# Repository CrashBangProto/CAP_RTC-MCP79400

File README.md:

#Toadstool-RTC79400

**Toadstool Cap - MCP79400 Real time clock**

The Toadstool family is made up of breadboard-friendly prototyping boards that house a microcontroller, and modules called *Caps* that connect using a standard header.  The prototyping board is analagous to an Arduino/Launchpad and the Cap analagous to a shield/boosterpack.

This repository contains the schematics for the **Toadstool-RTC79400 Cap**, a Real Time Clock module that connects to  Toadstool prototyping boards using the common header.  The Microchip MCP79400 chip does all the work.

The boards were layed out using [KiCad](http://www.kicad-pcb.org) - KiCad is open source and awesome.

There are a number of other CrashBangProto respositories containing the schematics for other Toadstool boards and Caps, as well as sample code to get you up and running.

Visit the [Toadstool Webpages](http://www.crash-bang.com/projects/toadstool/) for more information on the project.

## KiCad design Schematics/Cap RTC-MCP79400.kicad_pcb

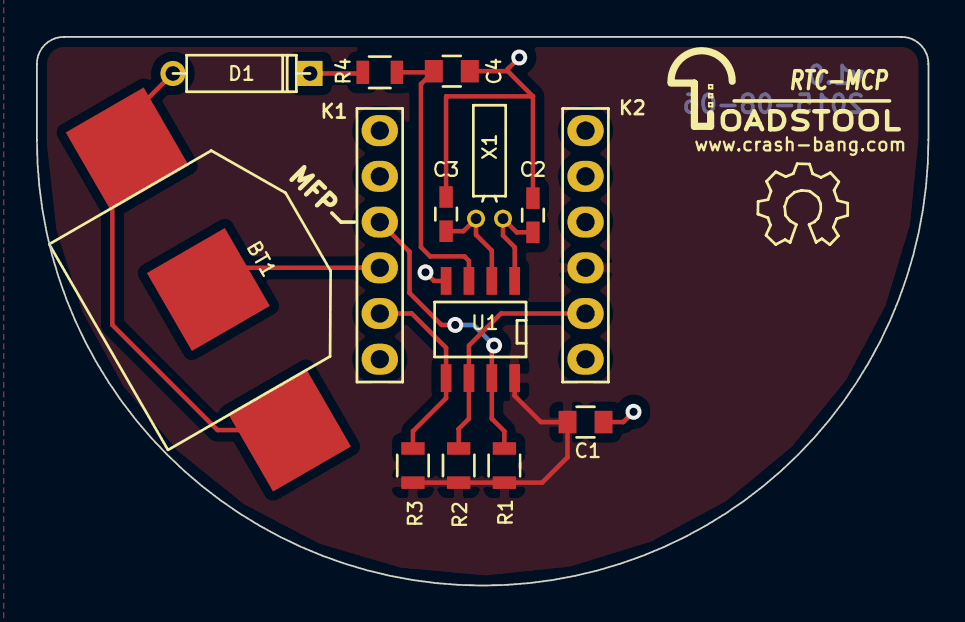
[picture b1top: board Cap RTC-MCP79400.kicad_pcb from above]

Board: 2 copper layers, 49.5 x 30.5 mm, 15 parts (0 on the bottom side), 10 nets.

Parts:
BT1: BATTERY; CR1220_Keystone_3000
C1: 0.1uF; C_0805
C2, C3: 8.2pF; C_0603_HandSoldering
C4: 100pF; C_0805
D1: DIODE; Diode_D3
K1: CAP_CONN_LHS; Socket_Strip_Stackable_1x06
K2: CAP_CONN_RHS; Socket_Strip_Stackable_1x06
R1: 10k; R_0805
R2, R3: 2.2k; R_0805
R4: 1k; R_0805
Toadstool_Logo: LOGO**; Toadstool_Logo
U1: MCP7400; SOIC-8-SN
X1: 32.768 kHz; Crystal_Round_Horizontal_2mm

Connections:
/SCL: K2.5, R2.2, U1.6
/SDA: K1.5, R3.2, U1.5
/SS2: K1.3, R1.2, U1.7
GND: BT1.2, C1.2, C2.2, C3.2, C4.1, K1.4, U1.4
unnamed: BT1.1, D1.1
unnamed: C2.1, U1.1, X1.2
unnamed: C3.1, U1.2, X1.1
unnamed: C4.2, R4.1, U1.3
unnamed: D1.2, R4.2
VCC: C1.1, K2.4, R1.1, R2.1, R3.1, U1.8

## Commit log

2015-05-15 :octocat: Added .gitattributes
2015-08-19 Cosmetic Changes to Silkscreen
    Cosmetic Changes to Silkscreen
2016-01-02 Silkscreen changes
    Added label to MFP pin
    New Gerber files generated
